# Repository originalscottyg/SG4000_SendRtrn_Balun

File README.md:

# SG4000_SendRtrn_Balun
KiCad Project - Balanced I/O PCB for SB4000 DIY project

This is a KiCad project to create a circuit and PCB to add balanced I/O to the External Sicdechain Send & Return on the Seprpent Audio "SB4000" DIY project.  I am not affiliated with Serpent Audio in any way.  I am using the repository as a versioning system for KiCad as I work out the circuit design and the PCB layout.

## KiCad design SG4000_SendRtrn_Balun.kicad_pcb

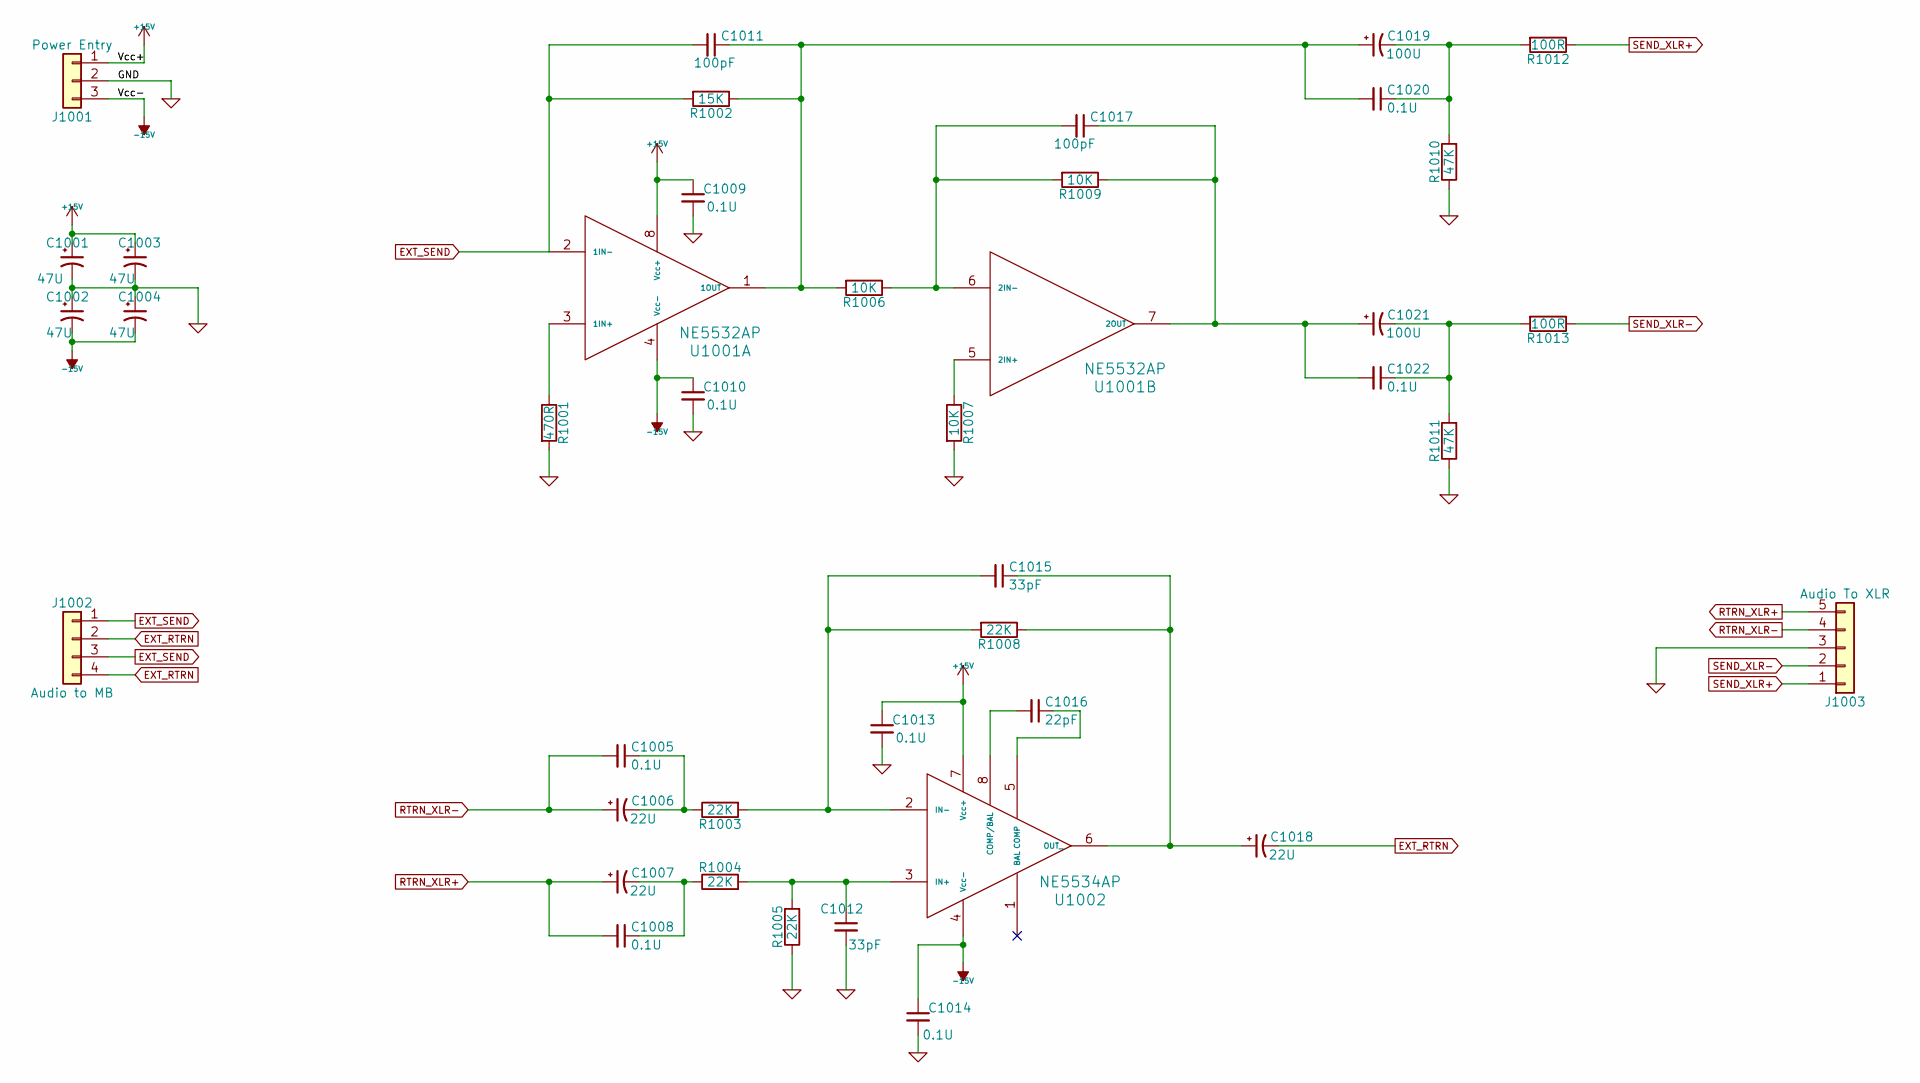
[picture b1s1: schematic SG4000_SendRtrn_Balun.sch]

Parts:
C1001, C1002, C1003, C1004: 47U; CP_Radial_D6.3mm_P2.50mm
C1005, C1008, C1009, C1010, C1013, C1014, C1020, C1022: 0.1U; C_Rect_L7.2mm_W4.5mm_P5.00mm_FKS2_FKP2_MKS2_MKP2
C1006, C1007, C1018: 22U; CP_Radial_D5.0mm_P2.00mm
C1011, C1017: 100pF; C_Rect_L4.0mm_W2.5mm_P2.50mm
C1012, C1015: 33pF; C_Rect_L4.0mm_W2.5mm_P2.50mm
C1016: 22pF; C_Rect_L4.0mm_W2.5mm_P2.50mm
C1019, C1021: 100U; CP_Radial_D8.0mm_P3.50mm
J1001: Power Entry; Pin_Header_Straight_1x03_Pitch2.54mm
J1002: Audio to MB; Pin_Header_Straight_1x04_Pitch2.54mm
J1003: Audio To XLR; Pin_Header_Straight_1x05_Pitch2.54mm
R1001: 470R; R_Axial_DIN0207_L6.3mm_D2.5mm_P10.16mm_Horizontal
R1002: 15K; R_Axial_DIN0207_L6.3mm_D2.5mm_P10.16mm_Horizontal
R1003, R1004, R1005, R1008: 22K; R_Axial_DIN0207_L6.3mm_D2.5mm_P10.16mm_Horizontal
R1006, R1007, R1009: 10K; R_Axial_DIN0207_L6.3mm_D2.5mm_P10.16mm_Horizontal
R1010, R1011: 47K; R_Axial_DIN0207_L6.3mm_D2.5mm_P10.16mm_Horizontal
R1012, R1013: 100R; R_Axial_DIN0207_L6.3mm_D2.5mm_P10.16mm_Horizontal
U1001: NE5532AP; DIP-8_W7.62mm
U1002: NE5534AP; DIP-8_W7.62mm

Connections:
+15V: C1001.1, C1003.1, C1009.1, C1013.1, J1001.1, U1001.8 (Vcc+), U1002.7 (Vcc+)
-15V: C1002.2, C1004.2, C1010.1, C1014.1, J1001.3, U1001.4 (Vcc-), U1002.4 (Vcc-)
EXT_RTRN: C1018.2, J1002.2, J1002.4
EXT_SEND: C1011.2, J1002.1, J1002.3, R1002.2, U1001.2 (1IN-)
GND: C1001.2, C1002.1, C1003.2, C1004.1, C1009.2, C1010.2, C1012.2, C1013.2, C1014.2, J1001.2, J1003.3, R1001.2, R1005.1, R1007.2, R1010.1, R1011.1
unnamed: C1005.1, C1006.2, R1003.1
unnamed: C1007.2, C1008.1, R1004.1
unnamed: C1011.1, C1019.1, C1020.2, R1002.1, R1006.2, U1001.1 (1OUT)
unnamed: C1012.1, R1004.2, R1005.2, U1002.3 (IN+)
unnamed: C1015.1, C1018.1, R1008.1, U1002.6 (OUT_)
unnamed: C1015.2, R1003.2, R1008.2, U1002.2 (IN-)
unnamed: C1016.1, U1002.5 (COMP)
unnamed: C1016.2, U1002.8 (COMP/BAL)
unnamed: C1017.1, C1021.1, C1022.2, R1009.1, U1001.7 (2OUT)
unnamed: C1017.2, R1006.1, R1009.2, U1001.6 (2IN-)
unnamed: C1019.2, C1020.1, R1010.2, R1012.2
unnamed: C1021.2, C1022.1, R1011.2, R1013.2
unnamed: R1001.1, U1001.3 (1IN+)
unnamed: R1007.1, U1001.5 (2IN+)
RTRN_XLR+: C1007.1, C1008.2, J1003.5
RTRN_XLR-: C1005.2, C1006.1, J1003.4
SEND_XLR+: J1003.1, R1012.1
SEND_XLR-: J1003.2, R1013.1

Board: 2 copper layers, 40 parts (0 on the bottom side), 23 nets, no tracks yet.

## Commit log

2017-09-19 Update README.md
    Initial readme copy.
2018-08-25 organization
